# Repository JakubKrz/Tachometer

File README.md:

# Digital Tachometer using PIC16F88 and Hall Effect Sensor
This project implements a digital tachometer using a PIC16F88 microcontroller and a Hall Effect sensor. The tachometer measures the rotational speed of a target object equipped with a magnet using the Hall Effect sensor to detect the magnet's passing.

## Components Used:
- PIC16F88 Microcontroller
- Hall Effect Sensor Module
- LCD Display (16x2)
- USB Power Socket for power input
- Magnet for the target object

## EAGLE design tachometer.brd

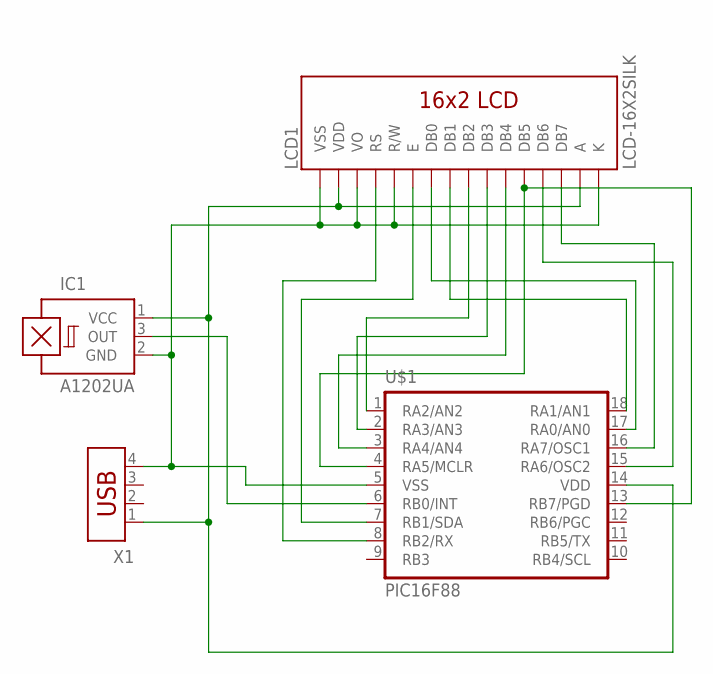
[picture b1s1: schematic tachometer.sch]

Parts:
IC1: A1202UA; SIP3-UA
LCD1: LCD-16X2SILK; LCD-16X2
U$1: PIC16F88; DIP18
X1: USB-787616; USB

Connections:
unnamed: IC1.1 (VCC), LCD1.2 (VDD), LCD1.15 (A), U$1.14 (VDD), X1.1
unnamed: IC1.2 (GND), LCD1.1 (VSS), LCD1.3 (VO), LCD1.5 (R/W), LCD1.16 (K), U$1.5 (VSS), X1.4
unnamed: IC1.3 (OUT), U$1.6 (RB0/INT)
unnamed: LCD1.8 (DB1), U$1.18 (RA1/AN1)
unnamed: LCD1.7 (DB0), U$1.17 (RA0/AN0)
unnamed: LCD1.14 (DB7), U$1.16 (RA7/OSC1)
unnamed: LCD1.13 (DB6), U$1.15 (RA6/OSC2)
unnamed: LCD1.9 (DB2), U$1.1 (RA2/AN2)
unnamed: LCD1.10 (DB3), U$1.2 (RA3/AN3)
unnamed: LCD1.11 (DB4), U$1.3 (RA4/AN4)
unnamed: LCD1.12 (DB5), U$1.4 (RA5/MCLR), U$1.13 (RB7/PGD)
unnamed: LCD1.6 (E), U$1.7 (RB1/SDA)
unnamed: LCD1.4 (RS), U$1.8 (RB2/RX)

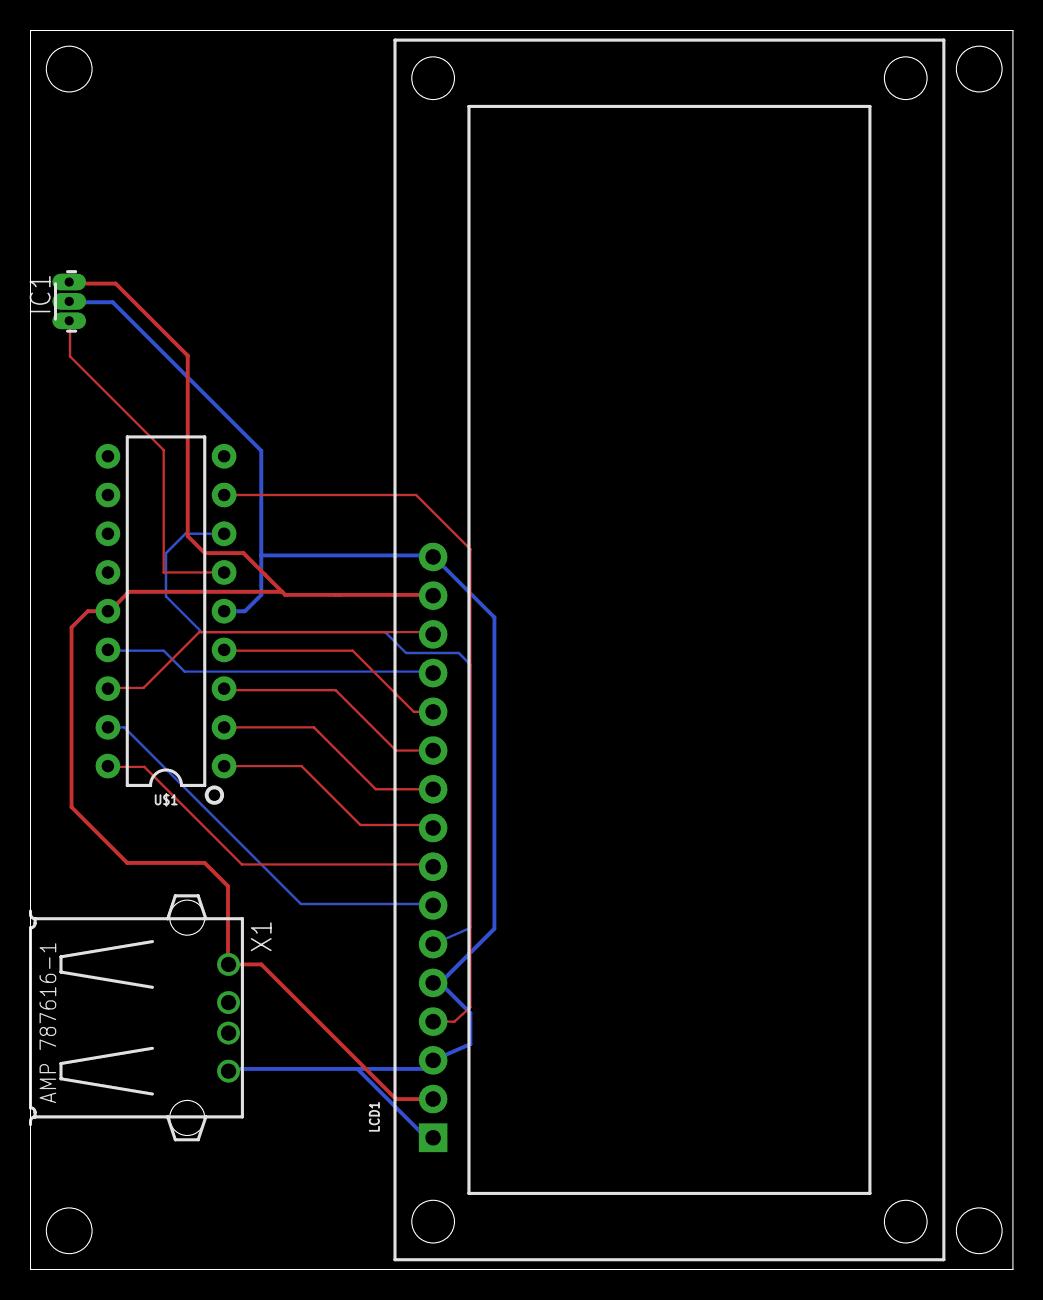
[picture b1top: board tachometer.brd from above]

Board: 2 copper layers, 64.4 x 81.3 mm, 4 parts (0 on the bottom side), 13 nets.

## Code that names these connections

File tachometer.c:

/*
 * File:   tachometer.c
 * Author: Jakub Krzyow?
 *
 * Created on 16 stycznia 2024, 12:38
 */

// CONFIG1
#pragma config FOSC = INTOSCIO  // Oscillator Selection bits (HS oscillator)
#pragma config WDTE = OFF       // Watchdog Timer Enable bit (WDT disabled)
#pragma config PWRTE = ON       // Power-up Timer Enable bit (PWRT enabled)
#pragma config MCLRE = OFF      // RA5/MCLR/VPP Pin Function Select bit (RA5/MCLR/VPP pin function is digital I/O, MCLR internally tied to VDD)
#pragma config BOREN = ON       // Brown-out Reset Enable bit (BOR enabled)
#pragma config LVP = OFF        // Low-Voltage Programming Enable bit (RB3 is digital I/O, HV on MCLR must be used for programming)
#pragma config CPD = OFF        // Data EE Memory Code Protection bit (Code protection off)
#pragma config WRT = OFF        // Flash Program Memory Write Enable bits (Write protection off)
#pragma config CCPMX = RB0      // CCP1 Pin Selection bit (CCP1 function on RB0)
#pragma config CP = OFF         // Flash Program Memory Code Protection bit (Code protection off)

// CONFIG2
#pragma config FCMEN = ON       // Fail-Safe Clock Monitor Enable bit (Fail-Safe Clock Monitor enabled)
#pragma config IESO = ON        // Internal External Switchover bit (Internal External Switchover mode enabled)

#include <xc.h>
#define _XTAL_FREQ 8000000
#define RS RB2
#define EN RB1
#define D4 RA4
#define D5 RB7
#define D6 RA6
#define D7 RA7

void Lcd_SetBit(char data_bit) //Based on the Hex value Set the Bits of the Data Lines
{
    if(data_bit& 1) 

        D4 = 1;

    else

        D4 = 0;


    if(data_bit& 2)

        D5 = 1;

    else

        D5 = 0;


    if(data_bit& 4)

        D6 = 1;

    else

        D6 = 0;


    if(data_bit& 8) 

        D7 = 1;

    else

        D7 = 0;
}

void Lcd_Cmd(char a)
{
    RS = 0;           

    Lcd_SetBit(a); //Incoming Hex value

    EN  = 1;         

        __delay_ms(4);

        EN  = 0;         
}

void Lcd_Clear()
{
    Lcd_Cmd(0); //Clear the LCD

    Lcd_Cmd(1); //Move the curser to first position
}

void Lcd_Set_Cursor(char a, char b)
{
    char temp,z,y;

    if(a== 1)

    {
      temp = 0x80 + b - 1; //80H is used to move the curser

        z = temp>>4; //Lower 8-bits

        y = temp & 0x0F; //Upper 8-bits

        Lcd_Cmd(z); //Set Row

        Lcd_Cmd(y); //Set Column
    }

    else if(a== 2)
    {
        temp = 0xC0 + b - 1;

        z = temp>>4; //Lower 8-bits

        y = temp & 0x0F; //Upper 8-bits

        Lcd_Cmd(z); //Set Row

        Lcd_Cmd(y); //Set Column
    }
}

void Lcd_Start()
{
  Lcd_SetBit(0x00);

  for(int i=1065244; i<=0; i--)  NOP();  

  Lcd_Cmd(0x03);

    __delay_ms(5);

  Lcd_Cmd(0x03);

    __delay_ms(11);

  Lcd_Cmd(0x03); 

  Lcd_Cmd(0x02); //02H is used for Return home -> Clears the RAM and initializes the LCD

  Lcd_Cmd(0x02); //02H is used for Return home -> Clears the RAM and initializes the LCD

  Lcd_Cmd(0x08); //Select Row 1

  Lcd_Cmd(0x00); //Clear Row 1 Display

  Lcd_Cmd(0x0C); //Select Row 2

  Lcd_Cmd(0x00); //Clear Row 2 Display

  Lcd_Cmd(0x06);
}

void Lcd_Print_Char(char data)
{
   char Lower_Nibble,Upper_Nibble;

   Lower_Nibble = data&0x0F;

   Upper_Nibble = data&0xF0;

   RS = 1;

   Lcd_SetBit(Upper_Nibble>>4);

   EN = 1;

   for(int i=2130483; i<=0; i--)  NOP(); 

   EN = 0;

   Lcd_SetBit(Lower_Nibble);

   EN = 1;

   for(int i=2130483; i<=0; i--)  NOP();

   EN = 0;
}

void Lcd_Print_String(char *a)
{
    int i;
    for(i=0;a[i]!='\0';i++)
       Lcd_Print_Char(a[i]);
}

volatile int overflow = 0;
volatile int rev = 0;
volatile uint16_t timestamp = 0;
volatile int ov_timestamp = 0;
char ch1,ch2,ch3,ch4;
int rpm = 0;
int speed = 0;

void __interrupt() ISR()
{
    if(TMR1IF)
    {
        overflow += 1;
        TMR1L = 0b11011011;
        TMR1H = 0b00001011;
        TMR1IF = 0;
    }
    if(INT0IF)
    {
        ov_timestamp = overflow;
        timestamp = (uint16_t)(TMR1H<<8) + TMR1L;
        overflow = 0;
        TMR1L = 0b11011011;
        TMR1H = 0b00001011; 
        rev += 1;
        INTF = 0; 
    }
}

void show_rpm() 
{
    ch1 = (rpm/1000)%10;
    ch2 = (rpm/100)%10;
    ch3 = (rpm/10)%10;
    ch4 = (rpm/1)%10;
            
    Lcd_Set_Cursor(1,9);
    Lcd_Print_Char(ch1+'0');
    Lcd_Print_Char(ch2+'0');
    Lcd_Print_Char(ch3+'0');
    Lcd_Print_Char(ch4+'0');
           
    ch1 = (speed/100)%10;
    ch2 = (speed/10)%10;
    ch3 = (speed/1)%10;
          
    Lcd_Set_Cursor(2,13);
    Lcd_Print_Char(ch1+'0');
    Lcd_Print_Char(ch2+'0');
    Lcd_Print_Char(',');
    Lcd_Print_Char(ch3+'0');
}
    int main()
    {
        IRCF0 = 1; //internal oscylator 8MHz
        IRCF1 = 1; //internal oscylator 8MHz
        IRCF2 = 1; //internal oscylator 8MHz
        ANSEL = 0b0000000;
        TRISA = 0x00;
        TRISB = 0x01;
        OPTION_REG = 0b00000000;
        RA0 =0;
        RA1 =0;
        RA2 =0;
        RA3 =0;
        //clock 62500 = 0.250s
        TMR1 = 0x0000;
        TMR1L = 0b11011011;
        TMR1H = 0b00001011;
        T1CONbits.T1CKPS = 0b11; //prescaler 1:8
        TMR1CS = 0; //internal clock
        TMR1IE = 1;
        TMR1ON = 1;
        
        GIE=1;     //Enable Global Interrupt
        PEIE=1;    //Enable the Peripheral Interrupt
        INTE = 1;  //Enable int0 interrupt
  
        Lcd_Start();
        Lcd_Clear();
                 
        Lcd_Set_Cursor(1,1);
        Lcd_Print_String("   RPM: ");
        Lcd_Set_Cursor(2,1);
        Lcd_Print_String("Speed(km/h): ");
        
    while(1)
    {
        __delay_ms(50);
        if(overflow > 8) //around 2s
        {
            overflow = 0;
            TMR1L = 0b11011011;
            TMR1H = 0b00001011; 
            rpm = 0;
            speed = 0;
            GIE = 0;
            show_rpm();
            GIE = 1;
        }
        if(rev>=1)
        {
            overflow = 0;
            rev = 0;
            timestamp = timestamp - 3035;
            float time = (float)(((float)ov_timestamp * 0.25) + ((float)timestamp / 250000));
            float rpmf = (float)(60) / time;
            rpm = (int)rpmf;
            //r = 34 cm
            // 0.37699 - pi and conversion to km/h
            speed = (int)(3.4 * rpmf * 0.37699); 
            GIE= 0;
            show_rpm();
            GIE = 1;
        }
    }
    return 0;
}
    
    

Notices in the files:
parts and their libraries:
SparkFun-Displays: Licensing: Creative Commons ShareAlike 4.0 International - https://creativecommons.org/licenses/by-sa/4.0
